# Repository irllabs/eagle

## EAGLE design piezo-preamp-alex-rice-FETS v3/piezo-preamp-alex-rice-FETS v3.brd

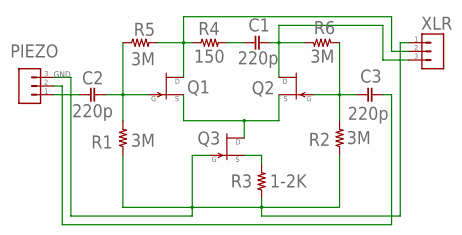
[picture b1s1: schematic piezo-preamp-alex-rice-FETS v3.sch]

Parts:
C1, C2, C3: 220p; C050-030X075
PIEZO: M03LOCK; 1X03_LOCK
Q1: 2N3819; TO92
Q2, Q3: 2N3819-WIDETO92_WIDE; TO92
R1, R2, R5, R6: 3M; 0204/5
R3: 1-2K; 0204/5
R4: 150; 0204/5
XLR: M03LOCK; 1X03_LOCK

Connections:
GND: PIEZO.3, Q3.2 (G), R1.1, R2.1, R3.1, XLR.1
unnamed: Q1.1 (D), R4.1, R5.2, XLR.2
unnamed: C1.2, Q2.1 (D), R6.2, XLR.3
unnamed: C1.1, R4.2
unnamed: C3.1, Q2.2 (G), R2.2, R6.1
unnamed: C2.2, Q1.2 (G), R1.2, R5.1
unnamed: Q3.3 (S), R3.2
unnamed: C2.1, PIEZO.1
unnamed: Q1.3 (S), Q2.3 (S), Q3.1 (D)
unnamed: C3.2, PIEZO.2

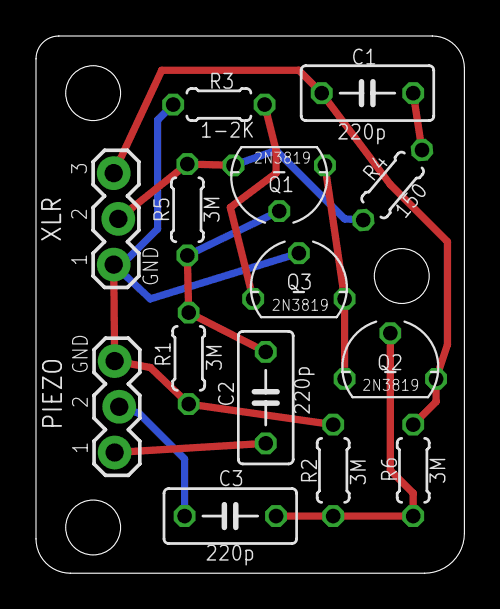
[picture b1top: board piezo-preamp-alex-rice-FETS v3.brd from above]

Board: 2 copper layers, 23.8 x 29.8 mm, 14 parts (0 on the bottom side), 10 nets.

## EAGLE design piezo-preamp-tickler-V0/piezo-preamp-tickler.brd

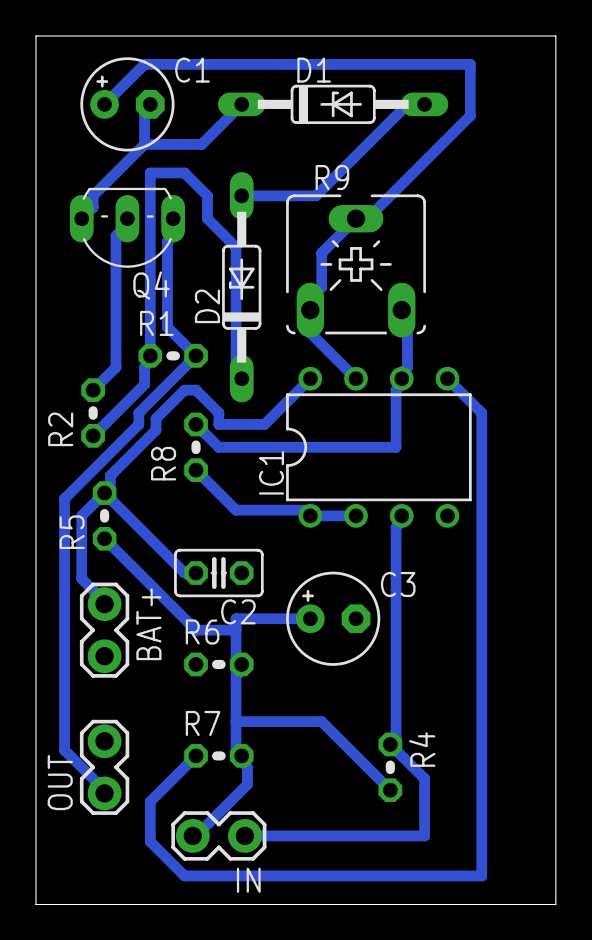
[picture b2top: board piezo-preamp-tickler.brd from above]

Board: 2 copper layers, 28.9 x 48.2 mm, 18 parts (0 on the bottom side), 13 nets.

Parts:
BAT+: 1X02_LOCK
C1, C3: 10u; E2,5-5
C2: 100n; C025-025X050
D1, D2: DO35Z10
IC1: TLC272; DIL08
IN: 1X02_LOCK
OUT: 1X02_LOCK
Q4: 2N5484; TO92-
R1: 10K; 0204V
R2: 0.3; 0204V
R4: 10k..10m; 0204V
R5: 150K; 0204V
R6: 100K; 0204V
R7, R8: 1K; 0204V
R9: CA6V

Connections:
GND: BAT+.2, C2.1, C3.-, IC1.4, OUT.2, R6.1
unnamed: D1.A, D2.A
unnamed: OUT.1, Q4.3, R1.2
unnamed: Q4.2, R2.2
unnamed: IC1.5, R7.1
unnamed: C1.+, IC1.7, R9.A, R9.S
unnamed: IC1.6, R8.2, R9.E
unnamed: C3.+, IN.2, R4.2, R5.1, R6.2, R7.2
unnamed: IC1.3, IN.1, R4.1
unnamed: C1.-, D1.C, Q4.1
unnamed: IC1.1, IC1.2, R8.1
R3: D2.C, R1.1, R2.1
V9V: BAT+.1, C2.2, IC1.8, R5.2

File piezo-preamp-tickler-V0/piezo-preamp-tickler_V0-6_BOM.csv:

"Part";"Value";"Device";"Package";"Description";"";
"BAT1";"";"BATTERYA23";"BATTERY-A23";"Battery Holders";"";
"C1";"10u";"CPOL-EUE2.5-5";"E2,5-5";"POLARIZED CAPACITOR, European symbol";"";
"C2";"100n";"C-EU025-025X050";"C025-025X050";"CAPACITOR, European symbol";"";
"C3";"10u";"CPOL-EUE2.5-5";"E2,5-5";"POLARIZED CAPACITOR, European symbol";"";
"D1";"";"1N821";"DO35Z10";"Reference DIODE";"";
"D2";"";"1N821";"DO35Z10";"Reference DIODE";"";
"IC1";"TLC272";"TLC272P";"DIL08";"OP AMP";"";
"IN";"";"M02LOCK";"1X02_LOCK";"Header 2";"";
"INPUT-SELECT";"";"M03LOCK";"1X03_LOCK";"Header 3";"";
"Q4";"2N5484";"2N5484";"TO92-";"N-Channel JFETs";"";
"R1";"10K";"R-US_0204/2V";"0204V";"RESISTOR, American symbol";"";
"R2";"1.2K";"R-US_0204/2V";"0204V";"RESISTOR, American symbol";"";
"R3";"1M";"R-US_0204/2V";"0204V";"RESISTOR, American symbol";"";
"R4";"10K";"R-US_0204/2V";"0204V";"RESISTOR, American symbol";"";
"R5";"150K";"R-US_0204/2V";"0204V";"RESISTOR, American symbol";"";
"R6";"100K";"R-US_0204/2V";"0204V";"RESISTOR, American symbol";"";
"R7";"1K";"R-US_0204/2V";"0204V";"RESISTOR, American symbol";"";
"R8";"1K";"R-US_0204/2V";"0204V";"RESISTOR, American symbol";"";
"R9";"";"TRIMPOT3386";"TRIM-3386";"SMT trimmer potentiometer part number TC33X";"";
"R10";"1K";"R-US_0204/2V";"0204V";"RESISTOR, American symbol";"";
"TO-HEADSET";"AUDIO-JACK3";"AUDIO-JACK3";"AUDIO-JACK-TRRS-SMD";"Audio jack - 3.5mm TRRS variety - two rings.";"";
"TO-PHONE";"AUDIO-JACK3";"AUDIO-JACK3";"AUDIO-JACK-TRRS-SMD";"Audio jack - 3.5mm TRRS variety - two rings.";"";

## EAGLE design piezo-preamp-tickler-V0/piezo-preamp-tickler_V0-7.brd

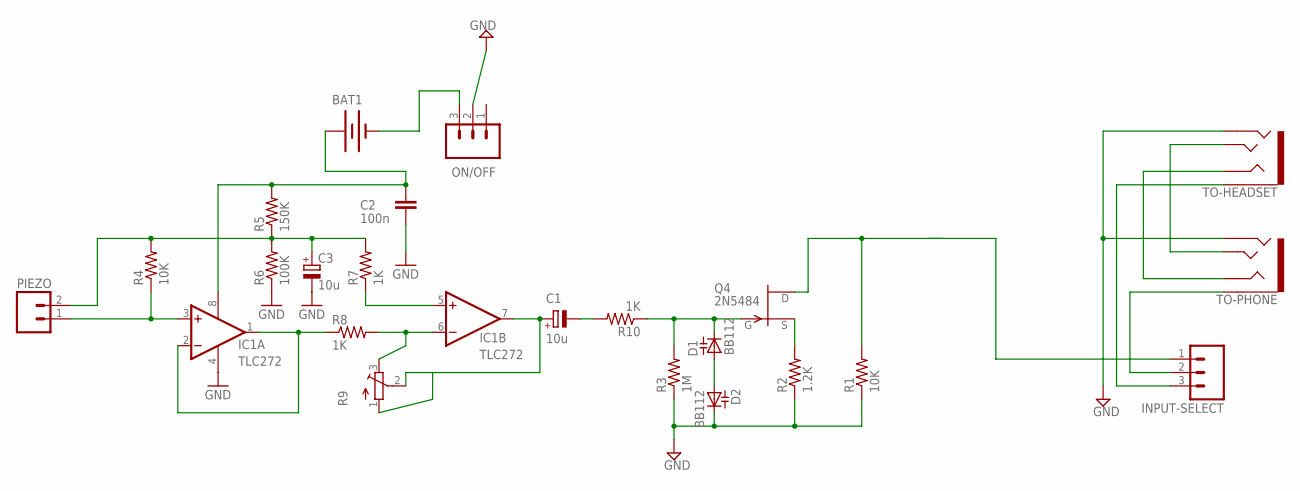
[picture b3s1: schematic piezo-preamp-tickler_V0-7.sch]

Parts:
BAT1: BATTERYA23; BATTERY-A23
C1, C3: 10u; E2,5-5
C2: 100n; C025-025X050
D1, D2: BB112; SOT54H
IC1: TLC272; DIL08
INPUT-SELECT: M03SINGLE-POLE-DOUBLE-THROW; SPDT-SWITCH
ON/OFF: labl; SPDT-SWITCH
PIEZO: M02LOCK; 1X02_LOCK
Q4: 2N5484; TO92-
R1, R4: 10K; 0204V
R2: 1.2K; 0204V
R3: 1M; 0204V
R5: 150K; 0204V
R6: 100K; 0204V
R7, R8, R10: 1K; 0204V
R9: TRIMPOT3386; TRIM-3386
TO-HEADSET: AUDIO-JACK3; AUDIO-JACK-TRRS-SMD
TO-PHONE: AUDIO-JACK3; AUDIO-JACK-TRRS-SMD

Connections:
GND: C2.1, C3.-, D2.C, IC1.4 (V-), ON/OFF.2, R1.1, R2.1, R3.1, R6.1, TO-HEADSET.RING2, TO-PHONE.RING2
unnamed: D1.A, D2.A
unnamed: BAT1.GND@1 (-), ON/OFF.3
unnamed: Q4.2 (S), R2.2
unnamed: IC1.5 (+IN), R7.1
unnamed: C1.+, IC1.7 (OUT), R9.1 (A), R9.2 (S)
unnamed: IC1.6 (-IN), R8.2, R9.3 (E)
unnamed: C3.+, PIEZO.2, R4.2, R5.1, R6.2, R7.2
unnamed: IC1.3 (+IN), PIEZO.1, R4.1
unnamed: D1.C, Q4.1 (G), R3.2, R10.1
unnamed: C1.-, R10.2
unnamed: INPUT-SELECT.3, TO-HEADSET.EARTH
unnamed: TO-HEADSET.TIP, TO-PHONE.TIP
unnamed: IC1.1 (OUT), IC1.2 (-IN), R8.1
unnamed: TO-HEADSET.RING1, TO-PHONE.RING1
TO-PHONE: INPUT-SELECT.2, TO-PHONE.EARTH
V9V: BAT1.PWR@1 (+), C2.2, IC1.8 (V+), R5.2
`DEL: INPUT-SELECT.1, Q4.3 (D), R1.2

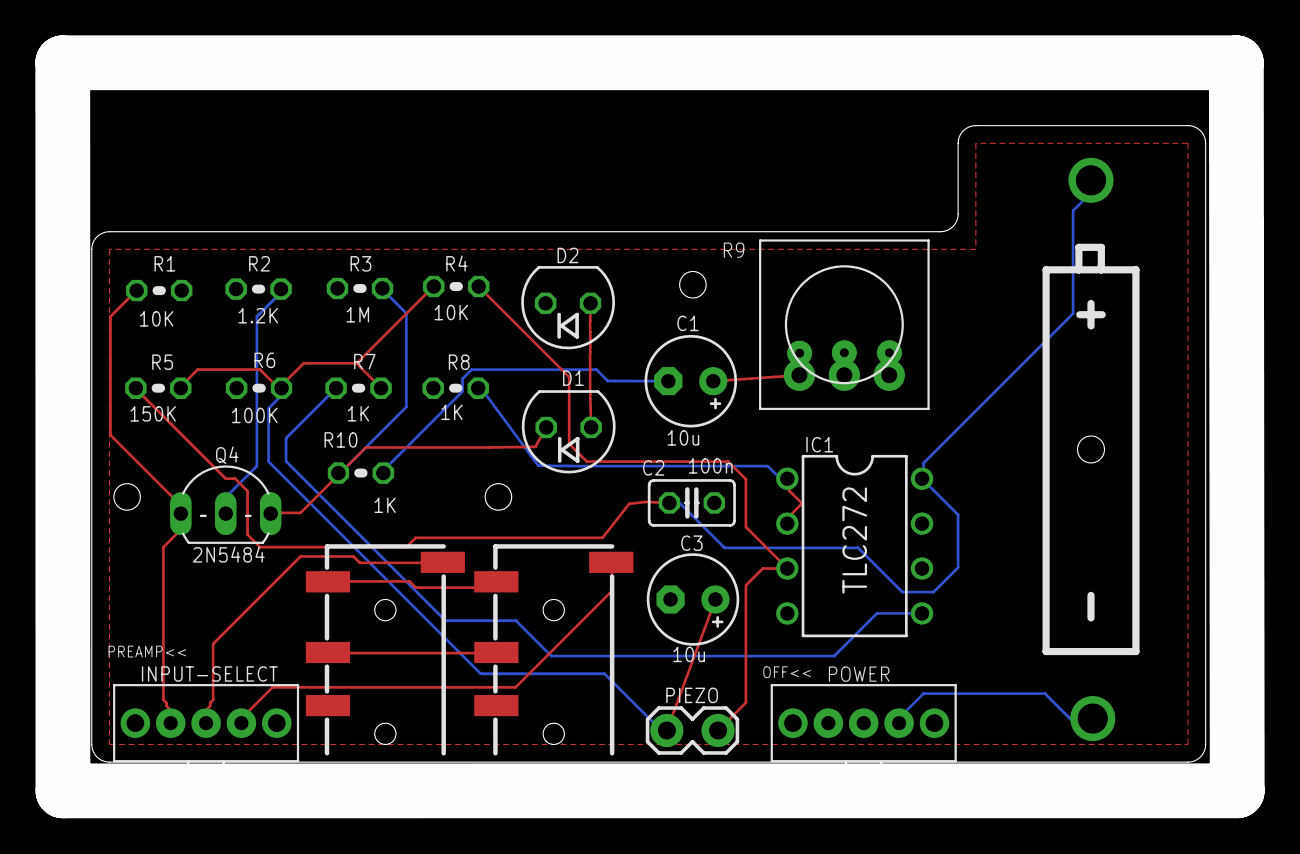
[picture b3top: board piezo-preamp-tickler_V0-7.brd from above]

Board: 2 copper layers, 66.4 x 41.2 mm, 23 parts (0 on the bottom side), 18 nets.

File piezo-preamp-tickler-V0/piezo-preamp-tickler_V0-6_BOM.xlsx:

Part | Value | Device | Package | Description
BAT1 |  | BATTERYA23 | BATTERY-A23 | Battery Holders
C1 | 10u | CPOL-EUE2.5-5 | E2,5-5 | POLARIZED CAPACITOR, European symbol | 732-8856-1-ND | 399-6597-ND
C2 | 100n | C-EU025-025X050 | C025-025X050 | CAPACITOR, European symbol | 445-5258-ND
C3 | 10u | CPOL-EUE2.5-5 | E2,5-5 | POLARIZED CAPACITOR, European symbol | 732-8856-1-ND | 399-6597-ND
D1 |  | 1N821 | DO35Z10 | Reference DIODE | 1N5221B - 63B
D2 |  | 1N821 | DO35Z10 | Reference DIODE | 1N5221B - 63B
IC1 | TLC272 | TLC272P | DIL08 | OP AMP | OPA2134PA-ND
IN |  | M02LOCK | 1X02_LOCK | Header 2
INPUT-SELECT |  | M03LOCK | 1X03_LOCK | Header 3
Q4 | 2N5484 | 2N5484 | TO92- | N-Channel JFETs
R1 | 10K | R-US_0204/2V | 0204V | RESISTOR, American symbol | 10.0KXBK-ND
R2 | 1.2K | R-US_0204/2V | 0204V | RESISTOR, American symbol | 1.2KADCT-ND
R3 | 1M | R-US_0204/2V | 0204V | RESISTOR, American symbol | 1.00MXBK-ND
R4 | 10K | R-US_0204/2V | 0204V | RESISTOR, American symbol | 10.0KXBK-ND
R5 | 150K | R-US_0204/2V | 0204V | RESISTOR, American symbol | 150KXBK-ND
R6 | 100K | R-US_0204/2V | 0204V | RESISTOR, American symbol | 100KXBK-ND
R7 | 1K | R-US_0204/2V | 0204V | RESISTOR, American symbol
R8 | 1K | R-US_0204/2V | 0204V | RESISTOR, American symbol
R9 |  | TRIMPOT3386 | TRIM-3386 | SMT trimmer potentiometer part number TC33X | 3352T-103LF-ND
R10 | 1K | R-US_0204/2V | 0204V | RESISTOR, American symbol
TO-HEADSET | AUDIO-JACK3 | AUDIO-JACK3 | AUDIO-JACK-TRRS-SMD | Audio jack - 3.5mm TRRS variety - two rings.
TO-PHONE | AUDIO-JACK3 | AUDIO-JACK3 | AUDIO-JACK-TRRS-SMD | Audio jack - 3.5mm TRRS variety - two rings.

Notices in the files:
parts and their libraries:
SparkFun-Connectors: Licensing: CC v3.0 Share-Alike You are welcome to use this library for commercial purposes.
SparkFun-Connectors: Licensing: Creative Commons ShareAlike 4.0 International - https://creativecommons.org/licenses/by-sa/4.0
